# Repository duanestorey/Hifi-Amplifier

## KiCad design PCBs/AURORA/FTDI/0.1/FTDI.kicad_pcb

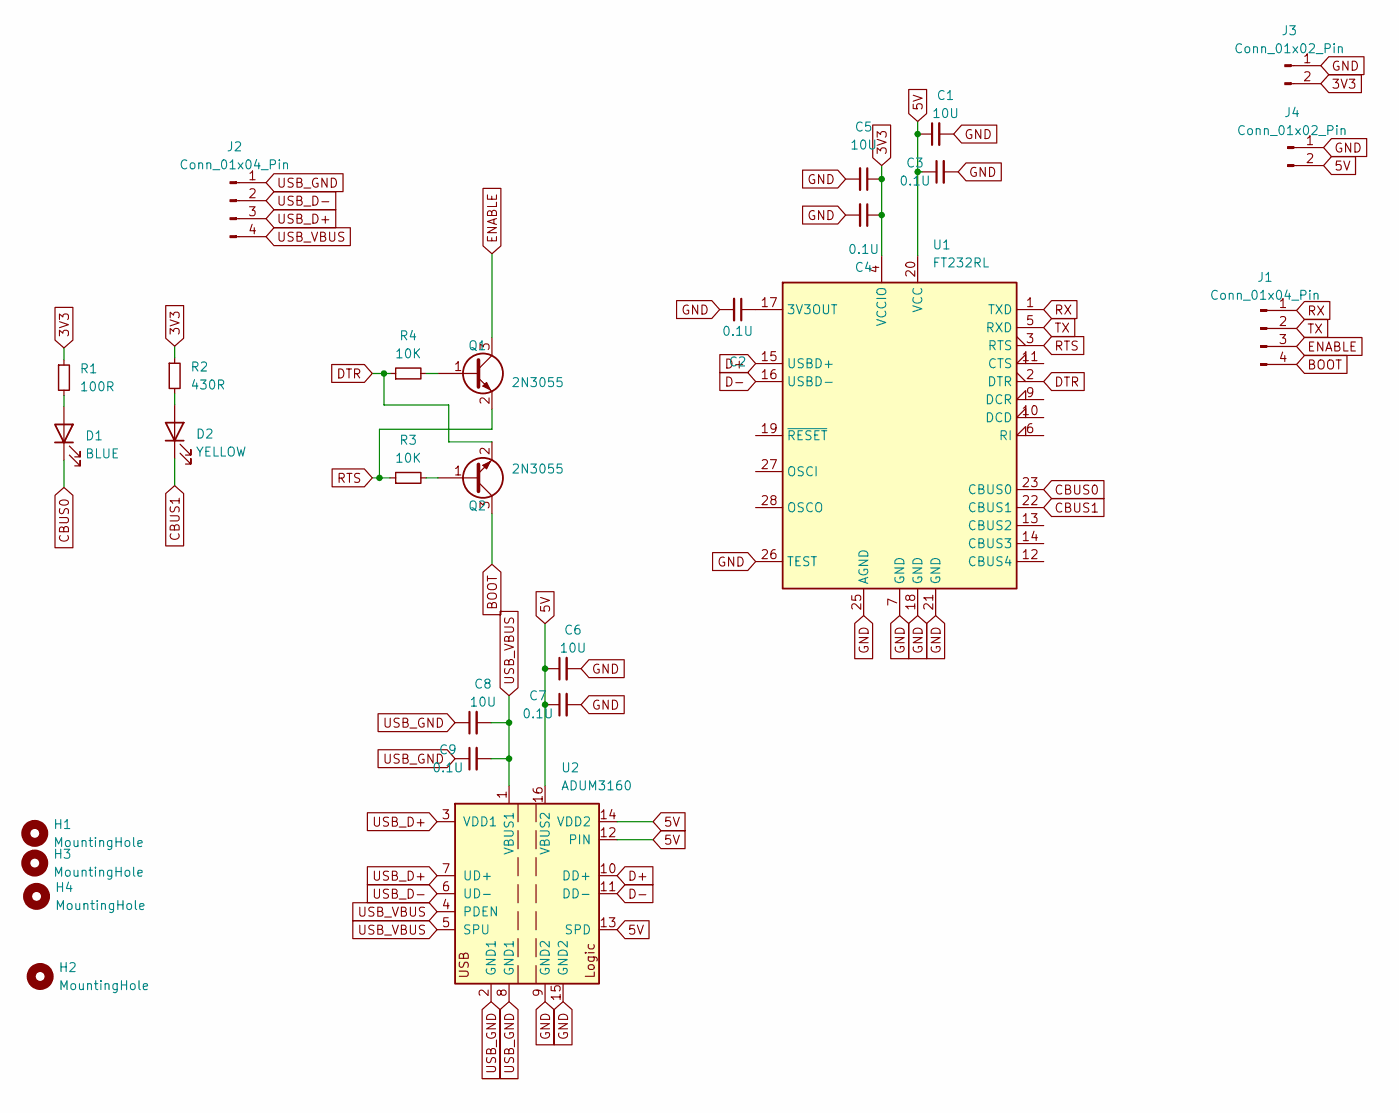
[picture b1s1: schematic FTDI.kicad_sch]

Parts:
C1, C5, C6, C8: 10U; C_1206_3216Metric_Pad1.33x1.80mm_HandSolder
C2, C3, C4, C7, C9: 0.1U; C_0805_2012Metric_Pad1.18x1.45mm_HandSolder
D1: BLUE; LED_0805_2012Metric_Pad1.15x1.40mm_HandSolder; LCSC XL-1608UBC-04
D2: YELLOW; LED_0805_2012Metric_Pad1.15x1.40mm_HandSolder; LCSC XL-1608UBC-04
H1, H2, H3, H4: MountingHole; MountingHole_3.2mm_M3
J1, J2: Conn_01x04_Pin; JST_PH_B4B-PH-K_1x04_P2.00mm_Vertical
J3, J4: Conn_01x02_Pin; JST_PH_B2B-PH-K_1x02_P2.00mm_Vertical
Q1, Q2: 2N3055; TSOT-23
R1: 100R; R_0603_1608Metric_Pad0.98x0.95mm_HandSolder
R2: 430R; R_0603_1608Metric_Pad0.98x0.95mm_HandSolder
R3, R4: 10K; R_0603_1608Metric_Pad0.98x0.95mm_HandSolder
U1: FT232RL; SSOP-28_5.3x10.2mm_P0.65mm
U2: ADUM3160; SOIC-16W_7.5x10.3mm_P1.27mm

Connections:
3V3: C4.1, C5.1, J3.2, R1.1, R2.1, U1.4 (VCCIO)
5V: C1.1, C3.1, C6.1, C7.1, J4.2, U1.20 (VCC), U2.12 (PIN), U2.13 (SPD), U2.14 (VDD2), U2.16 (VBUS2)
BOOT: J1.4, Q2.3 (C)
CBUS0: D1.1 (K), U1.23 (CBUS0)
CBUS1: D2.1 (K), U1.22 (CBUS1)
D+: U1.15 (USBD+), U2.10 (DD+)
D-: U1.16 (USBD-), U2.11 (DD-)
DTR: Q2.2 (E), R4.1, U1.2 (DTR)
ENABLE: J1.3, Q1.3 (C)
GND: C1.2, C2.2, C3.2, C4.2, C5.2, C6.2, C7.2, J3.1, J4.1, U1.7 (GND), U1.18 (GND), U1.21 (GND), U1.25 (AGND), U1.26 (TEST), U2.9 (GND2), U2.15 (GND2)
unnamed: D1.2 (A), R1.2
unnamed: D2.2 (A), R2.2
unnamed: Q1.1 (B), R4.2
unnamed: Q2.1 (B), R3.2
unnamed: C2.1, U1.17 (3V3OUT)
RTS: Q1.2 (E), R3.1, U1.3 (RTS)
RX: J1.1, U1.1 (TXD)
TX: J1.2, U1.5 (RXD)
USB_D+: J2.3, U2.3 (VDD1), U2.7 (UD+)
USB_D-: J2.2, U2.6 (UD-)
USB_GND: C8.1, C9.1, J2.1, U2.2 (GND1), U2.8 (GND1)
USB_VBUS: C8.2, C9.2, J2.4, U2.1 (VBUS1), U2.4 (PDEN), U2.5 (SPU)

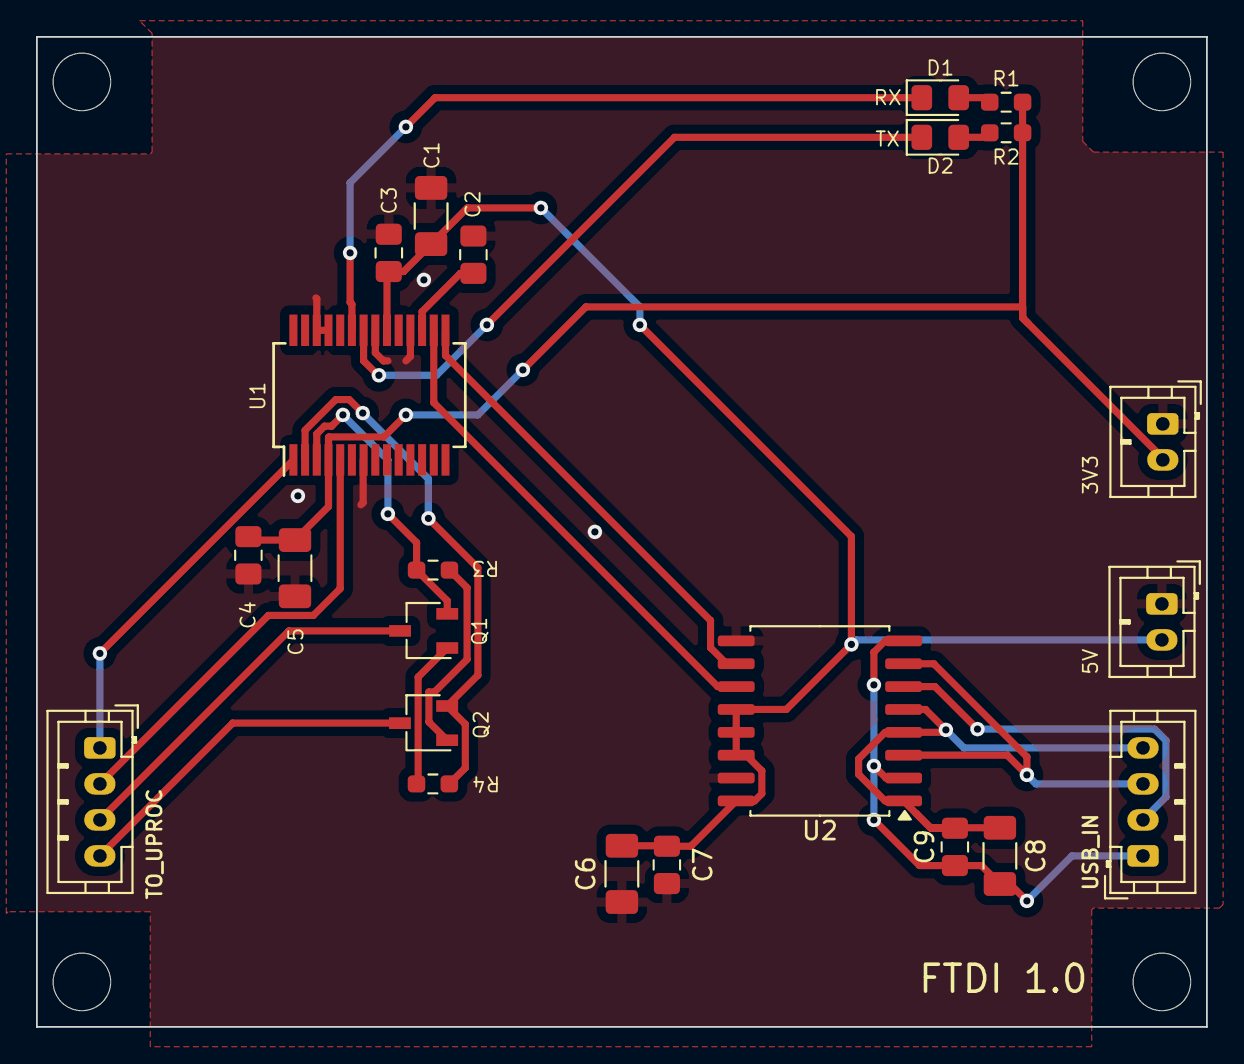
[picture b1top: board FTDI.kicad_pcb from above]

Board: 2 copper layers, 65.0 x 55.0 mm, 27 parts (0 on the bottom side), 22 nets.

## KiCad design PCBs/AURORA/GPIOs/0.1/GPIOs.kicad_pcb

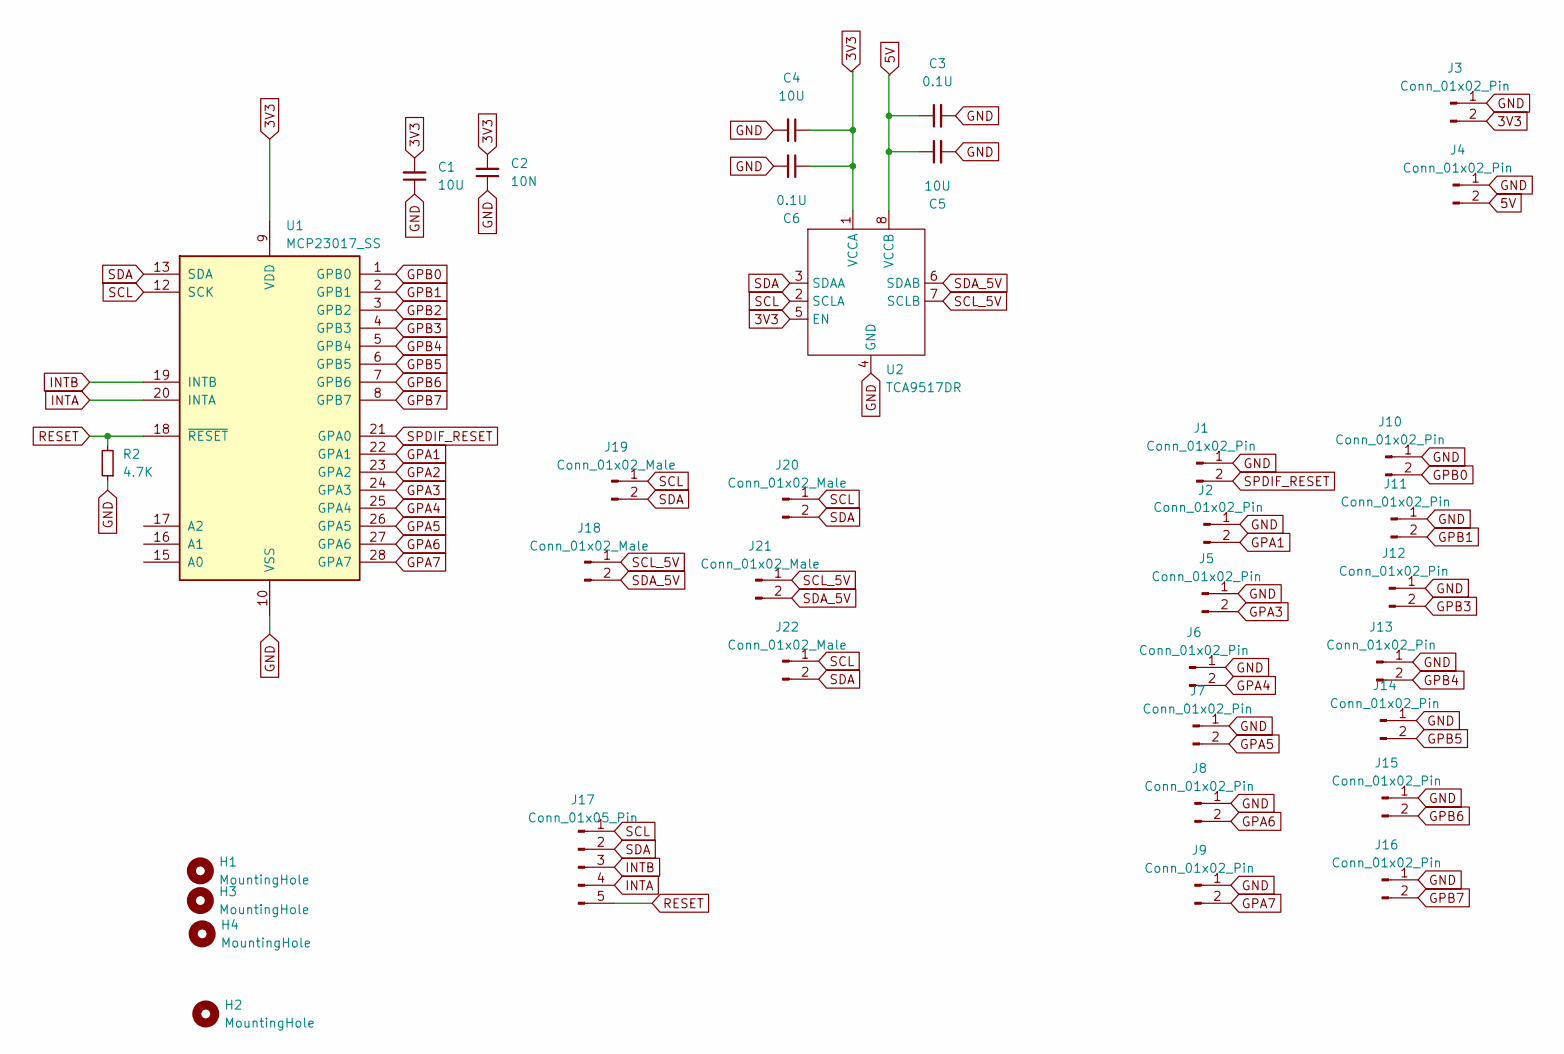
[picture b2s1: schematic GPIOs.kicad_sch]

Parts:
C1, C4, C5: 10U; C_1206_3216Metric_Pad1.33x1.80mm_HandSolder
C2: 10N; C_0805_2012Metric_Pad1.18x1.45mm_HandSolder
C3, C6: 0.1U; C_0805_2012Metric_Pad1.18x1.45mm_HandSolder
H1, H2, H3, H4: MountingHole; MountingHole_3.2mm_M3
J1, J2, J3, J4, J5, J6, J7, J8, J9, J10, J11, J12, J13, J14, J15, J16: Conn_01x02_Pin; JST_PH_B2B-PH-K_1x02_P2.00mm_Vertical
J17: Conn_01x05_Pin; JST_PH_B5B-PH-K_1x05_P2.00mm_Vertical
J18, J19, J20, J21, J22: Conn_01x02_Male; JST_PH_B2B-PH-K_1x02_P2.00mm_Vertical
R2: 4.7K; R_0603_1608Metric_Pad0.98x0.95mm_HandSolder
U1: MCP23017_SS; SSOP-28_5.3x10.2mm_P0.65mm
U2: TCA9517DR; SOIC-8_3.9x4.9mm_P1.27mm

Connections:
3V3: C1.2, C2.2, C4.1, C6.1, J3.2, U1.9 (VDD), U2.1 (VCCA), U2.5 (EN)
5V: C3.1, C5.1, J4.2, U2.8 (VCCB)
GND: C1.1, C2.1, C3.2, C4.2, C5.2, C6.2, J1.1, J2.1, J3.1, J4.1, J5.1, J6.1, J7.1, J8.1, J9.1, J10.1, J11.1, J12.1, J13.1, J14.1, J15.1, J16.1, R2.1, U1.10 (VSS), U2.4 (GND)
GPA1: J2.2, U1.22 (GPA1)
GPA2: U1.23 (GPA2)
GPA3: J5.2, U1.24 (GPA3)
GPA4: J6.2, U1.25 (GPA4)
GPA5: J7.2, U1.26 (GPA5)
GPA6: J8.2, U1.27 (GPA6)
GPA7: J9.2, U1.28 (GPA7)
GPB0: J10.2, U1.1 (GPB0)
GPB1: J11.2, U1.2 (GPB1)
GPB2: U1.3 (GPB2)
GPB3: J12.2, U1.4 (GPB3)
GPB4: J13.2, U1.5 (GPB4)
GPB5: J14.2, U1.6 (GPB5)
GPB6: J15.2, U1.7 (GPB6)
GPB7: J16.2, U1.8 (GPB7)
INTA: J17.4, U1.20 (INTA)
INTB: J17.3, U1.19 (INTB)
RESET: J17.5, R2.2, U1.18 (~RESET)
SCL: J17.1, J19.1, J20.1, J22.1, U1.12 (SCK), U2.2 (SCLA)
SCL_5V: J18.1, J21.1, U2.7 (SCLB)
SDA: J17.2, J19.2, J20.2, J22.2, U1.13 (SDA), U2.3 (SDAA)
SDA_5V: J18.2, J21.2, U2.6 (SDAB)
SPDIF_RESET: J1.2, U1.21 (GPA0)

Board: 2 copper layers, 35 parts (0 on the bottom side), 24 nets, no tracks yet.

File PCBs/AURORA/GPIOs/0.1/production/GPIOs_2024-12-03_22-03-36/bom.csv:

Designator,Footprint,Quantity,Value,LCSC Part #
C1,1206,1,10U,
C2,0805,1,10N,
"H1, H2, H3, H4",MountingHole_3.2mm_M3,4,MountingHole,
"J1, J10, J11, J12, J13, J14, J15, J16, J2, J5, J6, J7, J8, J9",JST_PH_B2B-PH-K_1x02_P2.00mm_Vertical,14,Conn_01x02_Pin,
J17,JST_PH_B5B-PH-K_1x05_P2.00mm_Vertical,1,Conn_01x05_Pin,
J3,JST_PH_S2B-PH-SM4-TB_1x02-1MP_P2.00mm_Horizontal,1,Conn_01x02_Pin,
J4,JST_PH_B2B-PH-SM4-TB_1x02-1MP_P2.00mm_Vertical,1,Conn_01x02_Pin,
R2,0603,1,4.7K,
U1,SSOP-28_5.3x10.2mm_P0.65mm,1,MCP23017_SS,

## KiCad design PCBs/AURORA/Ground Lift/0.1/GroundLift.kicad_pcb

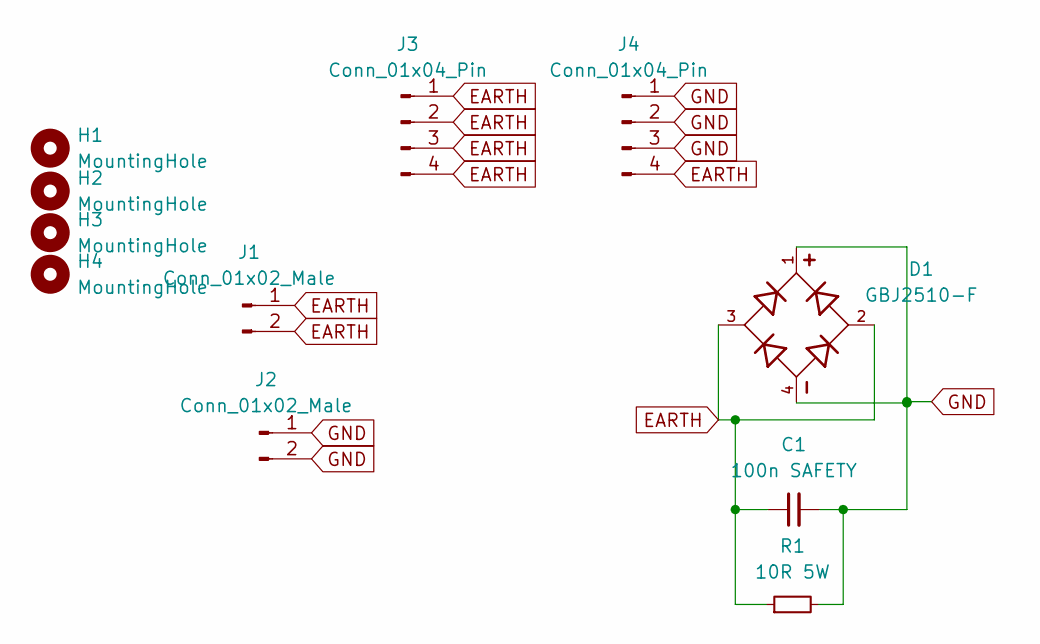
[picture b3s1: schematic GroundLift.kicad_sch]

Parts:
C1: 100n SAFETY; C_Rect_L18.0mm_W5.0mm_P15.00mm_FKS3_FKP3
D1: GBJ2510-F; Diode_Bridge_Vishay_DFS
H1, H2, H3, H4: MountingHole; MountingHole_3.2mm_M3
J1, J2: Conn_01x02_Male; JST_VH_B2P-VH-B_1x02_P3.96mm_Vertical
J3, J4: Conn_01x04_Pin; TerminalBlock_4Ucon_1x04_P3.50mm_Horizontal
R1: 10R 5W; R_2816_7142Metric_Pad3.20x4.45mm_HandSolder

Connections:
EARTH: C1.1, D1.2, D1.3, J1.1, J1.2, J3.1, J3.2, J3.3, J3.4, J4.4, R1.1
GND: C1.2, D1.1, D1.4, J2.1, J2.2, J4.1, J4.2, J4.3, R1.2

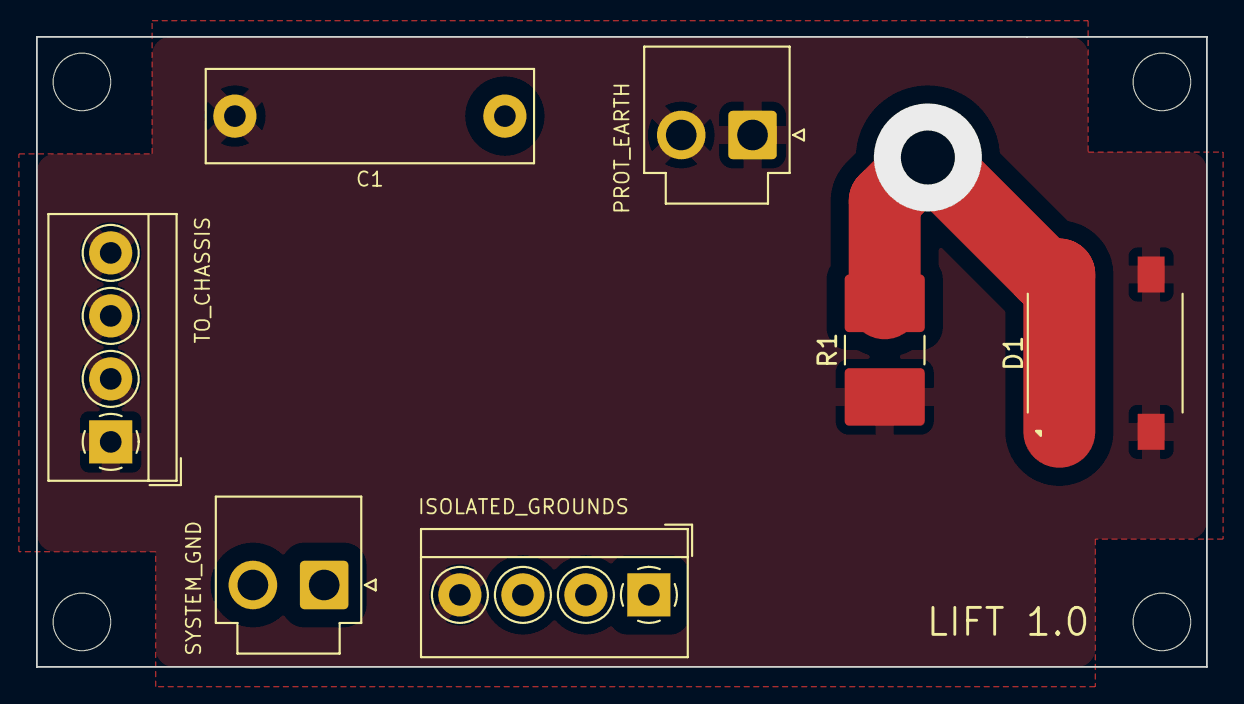
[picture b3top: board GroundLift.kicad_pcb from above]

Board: 2 copper layers, 65.0 x 35.0 mm, 11 parts (0 on the bottom side), 2 nets.

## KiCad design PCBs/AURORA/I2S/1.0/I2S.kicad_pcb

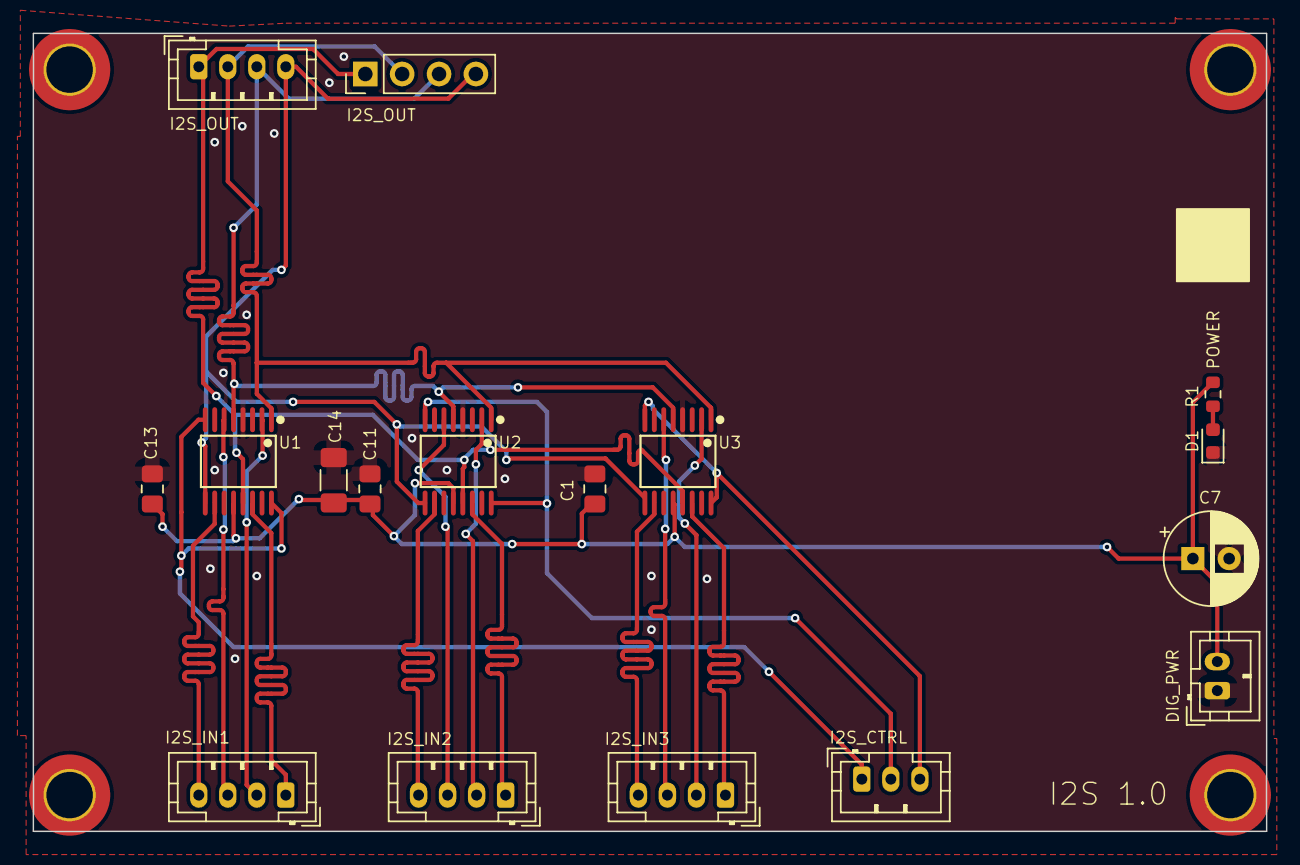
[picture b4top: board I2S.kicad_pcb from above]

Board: 2 copper layers, 85.0 x 55.0 mm, 21 parts (0 on the bottom side), 22 nets.

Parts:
C1, C11, C13: 0.1u; C_0805_2012Metric_Pad1.18x1.45mm_HandSolder
C7: 470u; CP_Radial_D6.3mm_P2.50mm
C14: 10u; C_1206_3216Metric_Pad1.33x1.80mm_HandSolder
D1: BLUE; LED_0603_1608Metric
H1, H2, H3, H4: MountingHole; MountingHole_3.2mm_M3_DIN965_Pad_TopOnly
J1, J4, J8, J9: Conn_01x04_Pin; JST_PH_B4B-PH-K_1x04_P2.00mm_Vertical
J2: Conn_01x02_Male; JST_PH_B2B-PH-K_1x02_P2.00mm_Vertical
J3: Conn_01x04_Pin; PinHeader_1x04_P2.54mm_Vertical
J5: Conn_01x03_Pin; JST_PH_B3B-PH-K_1x03_P2.00mm_Vertical
R1: 150R; R_0603_1608Metric
U1, U2, U3: TS3A44159PWR; TSSOP-16_L5.0-W4.4-P0.65-LS6.4-BL

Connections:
3V3: C1.1, C7.1, C11.1, C13.1, C14.1, J2.2, R1.1, U1.12 (VCC), U2.12 (VCC), U3.12 (VCC)
CONTROL1: J5.1, U1.8 (IN3-4), U1.16 (IN1-2)
CONTROL2: J5.2, U2.8 (IN3-4), U2.16 (IN1-2)
CONTROL3: J5.3, U3.8 (IN3-4), U3.16 (IN1-2)
GND: C1.2, C7.2, C11.2, C13.2, C14.2, D1.1 (K), J2.1, U1.4 (GND), U2.4 (GND), U3.4 (GND)
I2S1_BCLK: J1.2, U1.2 (COM2)
I2S1_DATA: J1.4, U1.10 (COM4)
I2S1_LRCLK: J1.3, U1.6 (COM3)
I2S1_MCLK: J1.1, U1.14 (COM1)
I2S2_BCLK: J9.2, U2.2 (COM2)
I2S2_DATA: J9.4, U2.10 (COM4)
I2S2_LRCLK: J9.3, U2.6 (COM3)
I2S2_LRCLK_OUT: J3.3, J8.3, U1.5 (NO3), U2.5 (NO3), U3.5 (NO3)
I2S2_MCLK: J9.1, U2.14 (COM1)
I2S3_BCLK: J4.2, U3.2 (COM2)
I2S3_DATA: J4.4, U3.10 (COM4)
I2S3_LRCLK: J4.3, U3.6 (COM3)
I2S3_MCLK: J4.1, U3.14 (COM1)
I2S_BCLK_OUT: J3.2, J8.2, U1.1 (NO2), U2.1 (NO2), U3.1 (NO2)
I2S_DATA_OUT: J3.4, J8.4, U1.9 (NO4), U2.9 (NO4), U3.9 (NO4)
I2S_MCLK_OUT: J3.1, J8.1, U1.13 (NO1), U2.13 (NO1), U3.13 (NO1)
unnamed: D1.2 (A), R1.2

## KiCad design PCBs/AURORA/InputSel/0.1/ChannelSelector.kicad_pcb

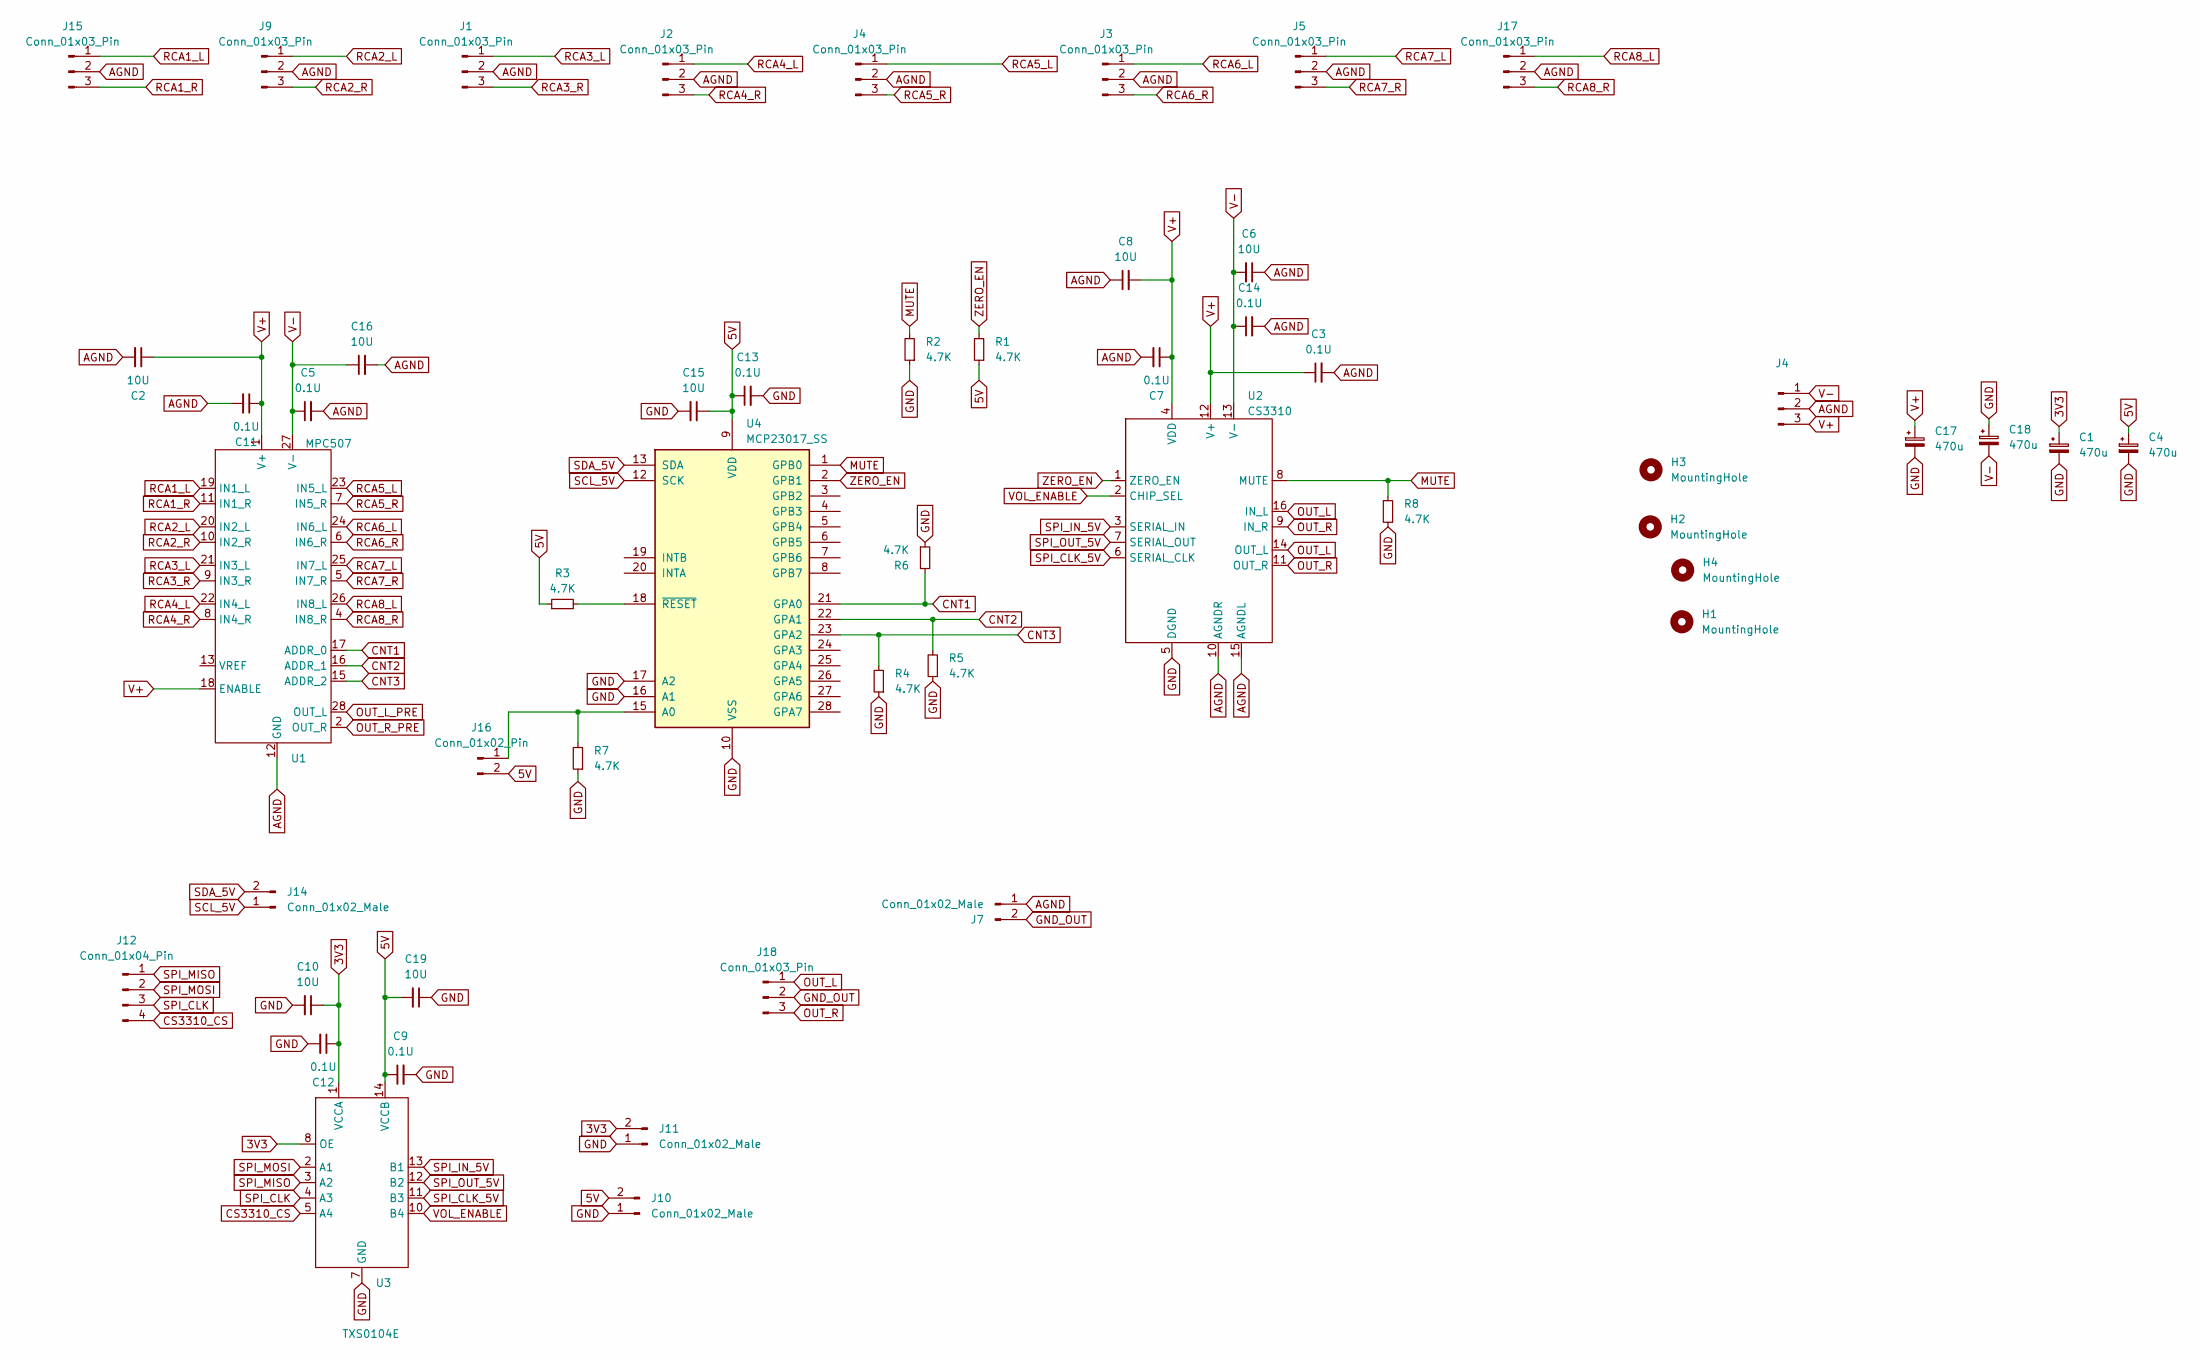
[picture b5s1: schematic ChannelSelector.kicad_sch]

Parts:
C1, C4, C17, C18: 470u; CP_Radial_D6.3mm_P2.50mm
C2, C6, C8, C10, C15, C16, C19: 10U; C_1206_3216Metric_Pad1.33x1.80mm_HandSolder
C3, C5, C7, C9, C11, C12, C13, C14: 0.1U; C_0805_2012Metric_Pad1.18x1.45mm_HandSolder
H1, H2, H3, H4: MountingHole; MountingHole_3.2mm_M3
J1, J2, J3, J4, J5, J9, J15, J17, J18: Conn_01x03_Pin; JST_PH_B3B-PH-K_1x03_P2.00mm_Vertical
J7: Conn_01x02_Male; PinHeader_1x02_P2.54mm_Vertical
J10, J11, J14: Conn_01x02_Male; JST_PH_B2B-PH-K_1x02_P2.00mm_Vertical
J12: Conn_01x04_Pin; JST_PH_B4B-PH-K_1x04_P2.00mm_Vertical
J16: Conn_01x02_Pin; PinHeader_1x02_P2.54mm_Vertical
R1, R2, R3, R4, R5, R6, R7, R8: 4.7K; R_0603_1608Metric_Pad0.98x0.95mm_HandSolder
U1: MPC507; SOIC-28W_7.5x18.7mm_P1.27mm
U2: CS3310; SOIC-16W_7.5x10.3mm_P1.27mm
U3: TXS0104E; TSSOP-14_4.4x5mm_P0.65mm
U4: MCP23017_SS; SSOP-28_5.3x10.2mm_P0.65mm

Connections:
3V3: C1.1, C10.1, C12.1, J11.2, U3.1 (VCCA), U3.8 (OE)
5V: C4.1, C9.1, C13.1, C15.1, C19.2, J10.2, J16.2, R1.1, R3.1, U3.14 (VCCB), U4.9 (VDD)
AGND: C2.2, C3.2, C5.2, C6.1, C7.2, C8.1, C11.2, C14.2, C16.2, J1.2, J2.2, J3.2, J4.2, J5.2, J7.1, J9.2, J15.2, J17.2, U1.12 (GND), U2.10 (AGNDR), U2.15 (AGNDL); also elsewhere on the board
CNT1: R6.2, U1.17 (ADDR_0), U4.21 (GPA0)
CNT2: R5.2, U1.16 (ADDR_1), U4.22 (GPA1)
CNT3: R4.2, U1.15 (ADDR_2), U4.23 (GPA2)
CS3310_CS: J12.4, U3.5 (A4)
GND: C1.2, C4.2, C9.2, C10.2, C12.2, C13.2, C15.2, C17.2, C18.1, C19.1, J10.1, J11.1, R2.1, R4.1, R5.1, R6.1, R7.1, R8.1, U2.5 (DGND), U3.7 (GND), U4.10 (VSS), U4.16 (A1), U4.17 (A2)
GND_OUT: J7.2, J18.2
MUTE: R2.2, R8.2, U2.8 (MUTE), U4.1 (GPB0)
unnamed: J16.1, R7.2, U4.15 (A0)
unnamed: R3.2, U4.18 (~RESET)
OUT_L: J18.1, U2.14 (OUT_L), U2.16 (IN_L)
OUT_L_PRE: U1.28 (OUT_L)
OUT_R: J18.3, U2.9 (IN_R), U2.11 (OUT_R)
OUT_R_PRE: U1.2 (OUT_R)
RCA1_L: J15.1, U1.19 (IN1_L)
RCA1_R: J15.3, U1.11 (IN1_R)
RCA2_L: J9.1, U1.20 (IN2_L)
RCA2_R: J9.3, U1.10 (IN2_R)
RCA3_L: J1.1, U1.21 (IN3_L)
RCA3_R: J1.3, U1.9 (IN3_R)
RCA4_L: J2.1, U1.22 (IN4_L)
RCA4_R: J2.3, U1.8 (IN4_R)
RCA6_L: J3.1, U1.24 (IN6_L)
RCA6_R: J3.3, U1.6 (IN6_R)
RCA7_L: J5.1, U1.25 (IN7_L)
RCA7_R: J5.3, U1.5 (IN7_R)
RCA8_L: J17.1, U1.26 (IN8_L)
RCA8_R: J17.3, U1.4 (IN8_R)
SCL_5V: J14.1, U4.12 (SCK)
SDA_5V: J14.2, U4.13 (SDA)
SPI_CLK: J12.3, U3.4 (A3)
SPI_CLK_5V: U2.6 (SERIAL_CLK), U3.11 (B3)
SPI_IN_5V: U2.3 (SERIAL_IN), U3.13 (B1)
SPI_MISO: J12.1, U3.3 (A2)
SPI_MOSI: J12.2, U3.2 (A1)
SPI_OUT_5V: U2.7 (SERIAL_OUT), U3.12 (B2)
VOL_ENABLE: U2.2 (CHIP_SEL), U3.10 (B4)
ZERO_EN: R1.2, U2.1 (ZERO_EN), U4.2 (GPB1)

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
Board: 4 copper layers, 51 parts (0 on the bottom side), 42 nets, no tracks yet.

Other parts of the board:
J13: Conn_01x03_Male; JST_PH_B3B-PH-K_1x03_P2.00mm_Vertical

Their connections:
AGND: J13.2; also elsewhere on the board

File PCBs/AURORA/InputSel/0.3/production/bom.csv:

Designator,Footprint,Quantity,Value,LCSC Part #
"C1, C17, C18, C4",CP_Radial_D6.3mm_P2.50mm,4,470u,
"C11, C13, C5",0805,3,0.1U,
"C15, C16, C2",1206,3,10U,
"H1, H2, H3, H4",MountingHole_3.2mm_M3,4,MountingHole,
"J1, J15, J17, J18, J2, J3, J4, J5, J6, J9",JST_PH_B3B-PH-K_1x03_P2.00mm_Vertical,10,Conn_01x03_Pin,
J13,JST_PH_B3B-PH-K_1x03_P2.00mm_Vertical,1,Conn_01x03_Male,
J14,JST_PH_B2B-PH-K_1x02_P2.00mm_Vertical,1,Conn_01x02_Male,
J16,PinHeader_1x02_P2.54mm_Vertical,1,Conn_01x02_Pin,
J7,PinHeader_1x02_P2.54mm_Vertical,1,Conn_01x02_Male,
"R1, R2, R3, R4, R5, R6, R7",0603,7,4.7K,
U1,SOIC-28W_7.5x18.7mm_P1.27mm,1,MPC507,
U4,SSOP-28_5.3x10.2mm_P0.65mm,1,MCP23017_SS,

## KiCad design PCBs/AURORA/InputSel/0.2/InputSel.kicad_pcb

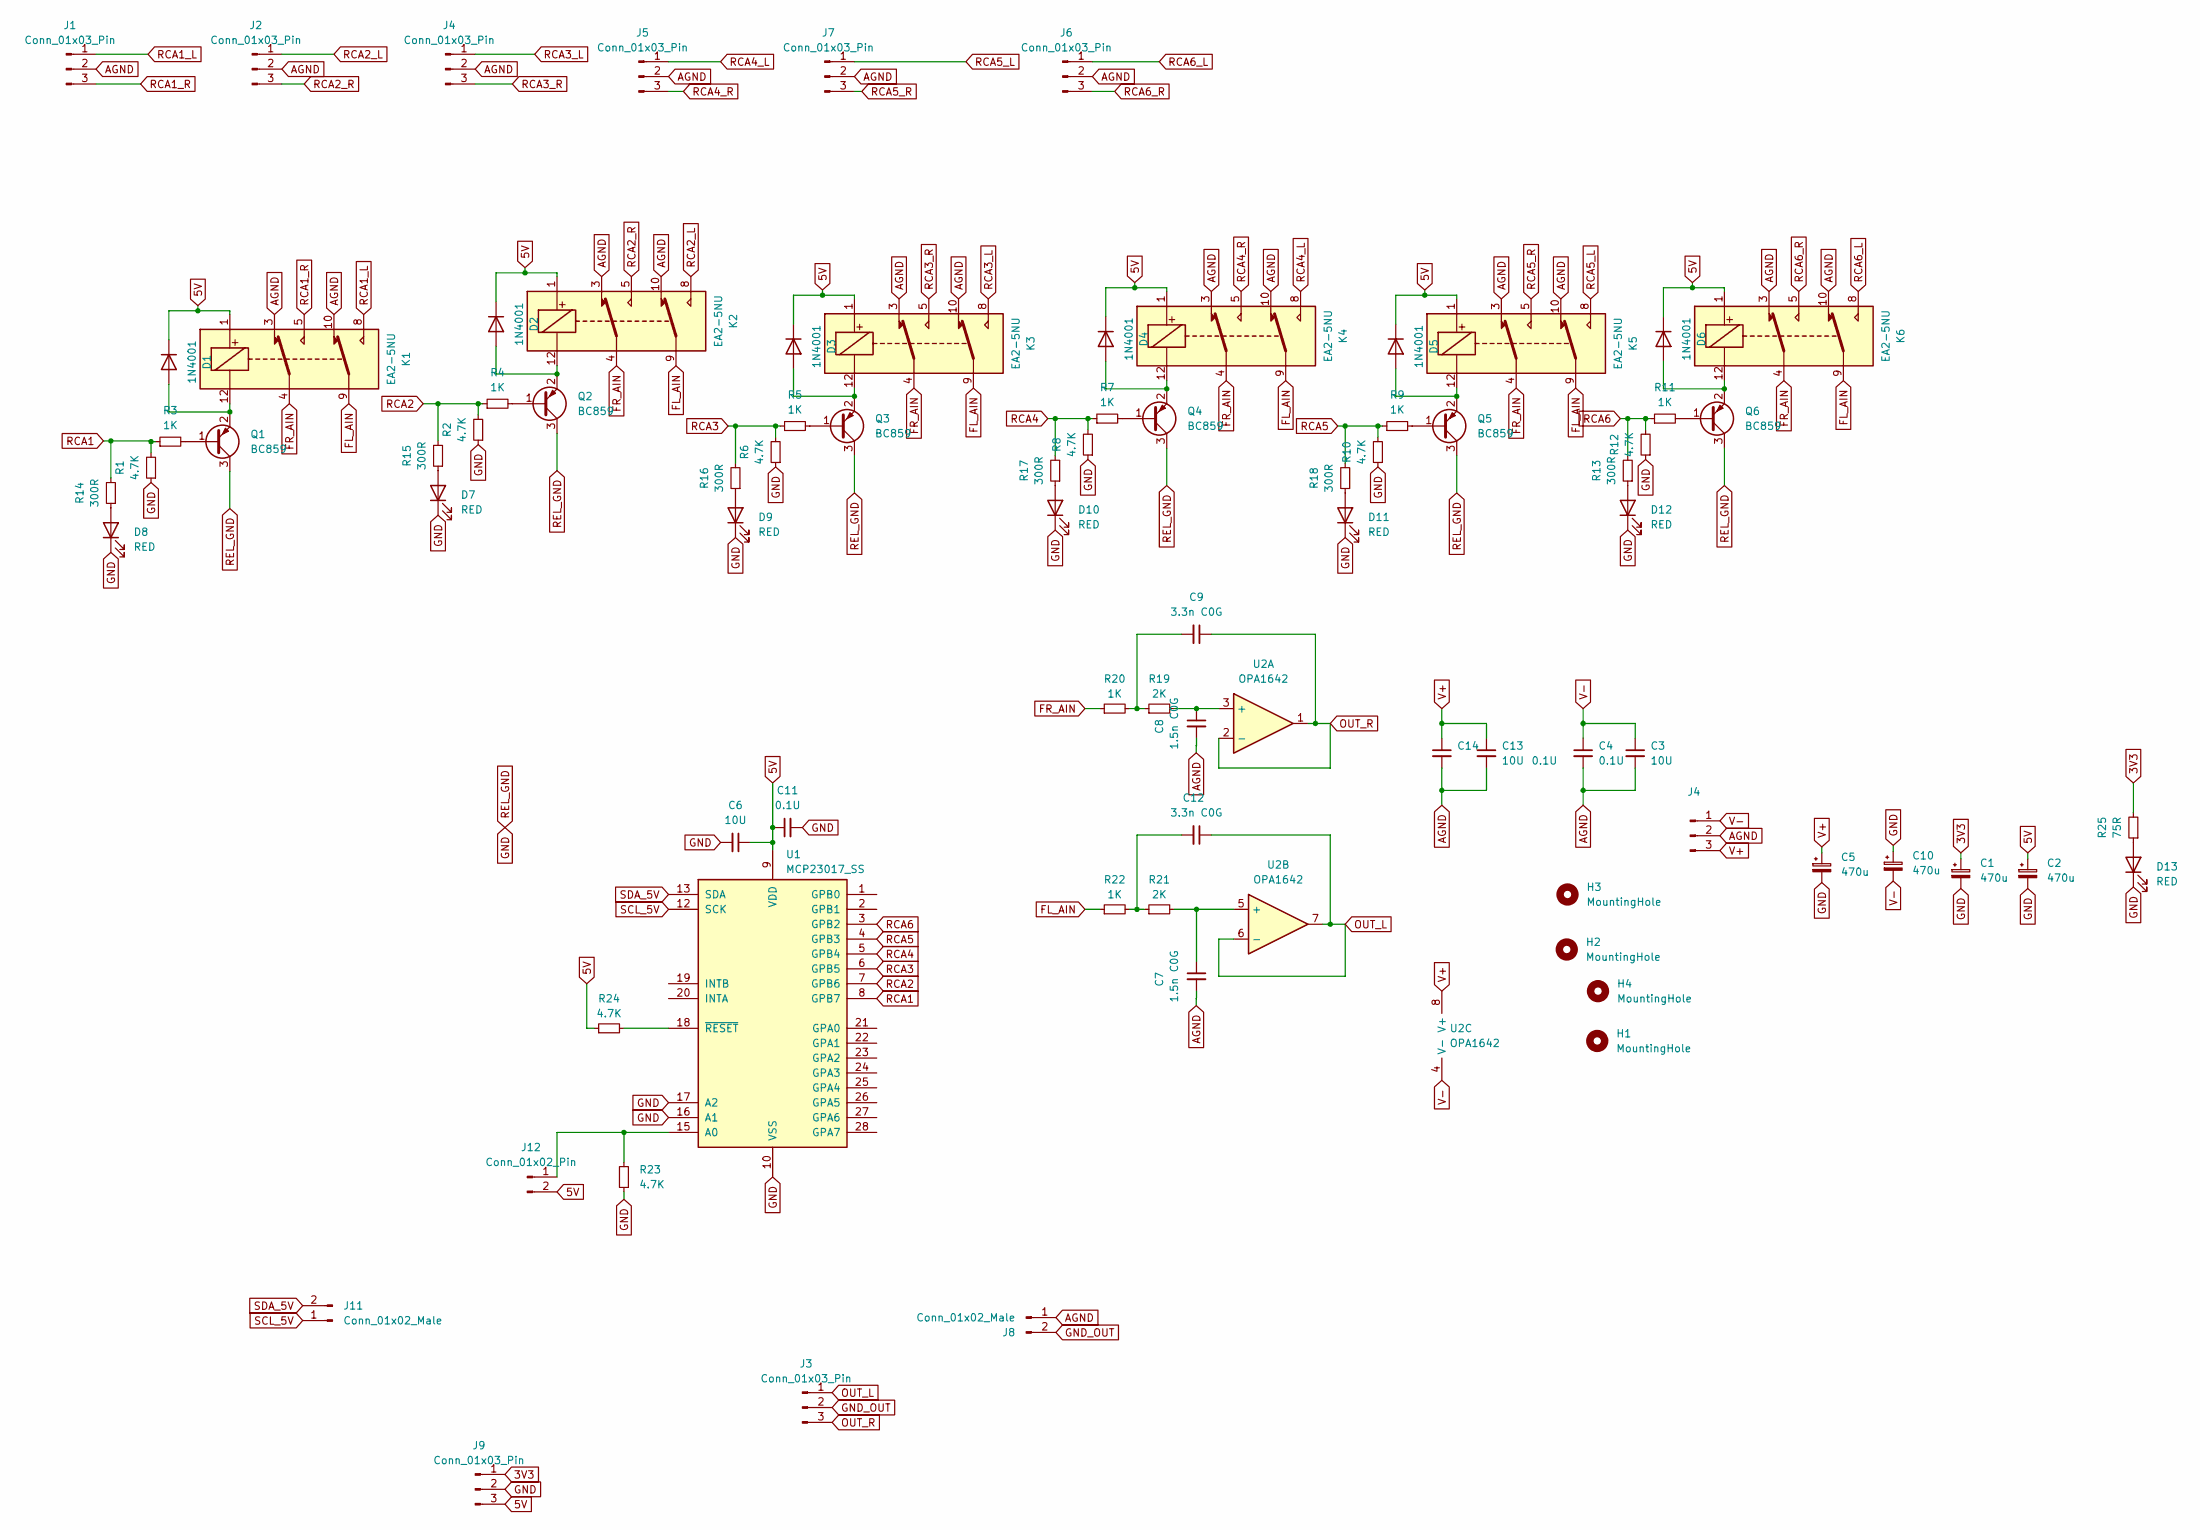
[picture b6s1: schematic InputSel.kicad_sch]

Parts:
C1, C2, C5, C10: 470u; CP_Radial_D6.3mm_P2.50mm
C3, C6, C13: 10U; C_1206_3216Metric_Pad1.33x1.80mm_HandSolder
C4, C11, C14: 0.1U; C_0805_2012Metric_Pad1.18x1.45mm_HandSolder
C7, C8: 1.5n C0G; C_0805_2012Metric_Pad1.18x1.45mm_HandSolder
C9, C12: 3.3n C0G; C_0805_2012Metric_Pad1.18x1.45mm_HandSolder
D1, D2, D3, D4, D5, D6: 1N4001; D_SMA
D7, D8, D9, D10, D11, D12, D13: RED; LED_0805_2012Metric
H1, H2, H3, H4: MountingHole; MountingHole_3.2mm_M3
J1, J2, J3, J5, J6, J7, J9: Conn_01x03_Pin; JST_PH_B3B-PH-K_1x03_P2.00mm_Vertical
J4: Conn_01x03_Male; JST_PH_B3B-PH-K_1x03_P2.00mm_Vertical
J8: Conn_01x02_Male; PinHeader_1x02_P2.54mm_Vertical
J11: Conn_01x02_Male; JST_PH_B2B-PH-K_1x02_P2.00mm_Vertical
J12: Conn_01x02_Pin; PinHeader_1x02_P2.54mm_Vertical
K1, K2, K3, K4, K5, K6: EA2-5NU; KEMET EA2
Q1, Q2, Q3, Q4, Q5, Q6: BC859; SOT-23
R1, R2, R6, R8, R10, R12, R23, R24: 4.7K; R_0603_1608Metric_Pad0.98x0.95mm_HandSolder
R3, R4, R5, R7, R9, R11, R20, R22: 1K; R_0603_1608Metric_Pad0.98x0.95mm_HandSolder
R13, R14, R15, R16, R17, R18: 300R; R_0603_1608Metric_Pad0.98x0.95mm_HandSolder
R19, R21: 2K; R_0603_1608Metric_Pad0.98x0.95mm_HandSolder
R25: 75R; R_0603_1608Metric_Pad0.98x0.95mm_HandSolder
U1: MCP23017_SS; SSOP-28_5.3x10.2mm_P0.65mm
U2: OPA1642; VSSOP-8_3x3mm_P0.65mm

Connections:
3V3: C1.1, J9.1, R25.2
5V: C2.1, C6.1, C11.1, D1.1 (K), D2.1 (K), D3.1 (K), D4.1 (K), D5.1 (K), D6.1 (K), J9.3, J12.2, K1.1, K2.1, K3.1, K4.1, K5.1, K6.1, R24.1, U1.9 (VDD)
AGND: C3.2, C4.2, C7.2, C8.2, C13.2, C14.2, J1.2, J2.2, J4.2, J5.2, J6.2, J7.2, J8.1, K1.3, K1.10, K2.3, K2.10, K3.3, K3.10, K4.3, K4.10, K5.3, K5.10, K6.3, K6.10; also elsewhere on the board
FL_AIN: K1.9, K2.9, K3.9, K4.9, K5.9, K6.9, R22.1
FR_AIN: K1.4, K2.4, K3.4, K4.4, K5.4, K6.4, R20.1
GND: C1.2, C2.2, C5.2, C6.2, C10.1, C11.2, D7.1 (K), D8.1 (K), D9.1 (K), D10.1 (K), D11.1 (K), D12.1 (K), D13.1 (K), J9.2, Q1.3 (C), Q2.3 (C), Q3.3 (C), Q4.3 (C), Q5.3 (C), Q6.3 (C), R1.1, R2.1, R6.1, R8.1, R10.1, R12.1, R23.1, U1.10 (VSS), U1.16 (A1), U1.17 (A2)
GND_OUT: J3.2, J8.2
unnamed: C9.2, R19.1, R20.2
unnamed: C12.2, R21.1, R22.2
unnamed: D1.2 (A), K1.12, Q1.2 (E)
unnamed: D2.2 (A), K2.12, Q2.2 (E)
unnamed: D3.2 (A), K3.12, Q3.2 (E)
unnamed: D4.2 (A), K4.12, Q4.2 (E)
unnamed: D5.2 (A), K5.12, Q5.2 (E)
unnamed: D6.2 (A), K6.12, Q6.2 (E)
unnamed: D7.2 (A), R15.1
unnamed: D8.2 (A), R14.1
unnamed: D9.2 (A), R16.1
unnamed: D10.2 (A), R17.1
unnamed: D11.2 (A), R18.1
unnamed: D12.2 (A), R13.1
unnamed: D13.2 (A), R25.1
unnamed: J12.1, R23.2, U1.15 (A0)
unnamed: Q1.1 (B), R3.2
unnamed: Q2.1 (B), R4.2
unnamed: Q3.1 (B), R5.2
unnamed: Q4.1 (B), R7.2
unnamed: Q5.1 (B), R9.2
unnamed: Q6.1 (B), R11.2
unnamed: R24.2, U1.18 (~RESET)
unnamed: C8.1, R19.2, U2.3 (+)
unnamed: C7.1, R21.2, U2.5 (+)
OUT_L: C12.1, J3.1, U2.6 (-), U2.7
OUT_R: C9.1, J3.3, U2.1, U2.2 (-)
RCA1: R1.2, R3.1, R14.2, U1.8 (GPB7)
RCA1_L: J1.1, K1.8
RCA1_R: J1.3, K1.5
RCA2: R2.2, R4.1, R15.2, U1.7 (GPB6)
RCA2_L: J2.1, K2.8
RCA2_R: J2.3, K2.5
RCA3: R5.1, R6.2, R16.2, U1.6 (GPB5)
RCA4: R7.1, R8.2, R17.2, U1.5 (GPB4)
RCA4_L: J5.1, K4.8
RCA4_R: J5.3, K4.5
RCA5: R9.1, R10.2, R18.2, U1.4 (GPB3)
RCA5_L: J7.1, K5.8
RCA5_R: J7.3, K5.5
RCA6: R11.1, R12.2, R13.2, U1.3 (GPB2)
RCA6_L: J6.1, K6.8
RCA6_R: J6.3, K6.5
SCL_5V: J11.1, U1.12 (SCK)
SDA_5V: J11.2, U1.13 (SDA)

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
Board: 4 copper layers, 82 parts (0 on the bottom side), 56 nets, no tracks yet.

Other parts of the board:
J10: Conn_01x03_Male; JST_PH_B3B-PH-K_1x03_P2.00mm_Vertical

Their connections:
AGND: J10.2; also elsewhere on the board
